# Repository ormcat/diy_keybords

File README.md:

ErgoFine
====

## 特徴
- 左右分割
- 60%
- カラムスタッカード
- ロープロファイル (Kailh Choc V1 専用)
- 狭ピッチ (18x17 MBK キャップのサイズ)

## 設計のポイント

数字行を設け、キー数に余裕をもたせたロープロファイルな 60% キーボードです。

FR4 とアクリルを積層し、硬い打鍵感を目指しました。
スイッチプレートと基盤の間にはシリコンシートを挟めると音が落ち着くかもしれません。

※基盤製造後に KiCad データを若干調整したため、なにかしら不備があるかもしれません。

---

Designed by ormcat

基盤は [自作キーボード設計入門](https://booth.pm/ja/items/1044084) を読みながら設計しました。  
KiCad シンボル、フットプリントは [foostan/kbd](https://github.com/foostan/kbd) を利用しました。

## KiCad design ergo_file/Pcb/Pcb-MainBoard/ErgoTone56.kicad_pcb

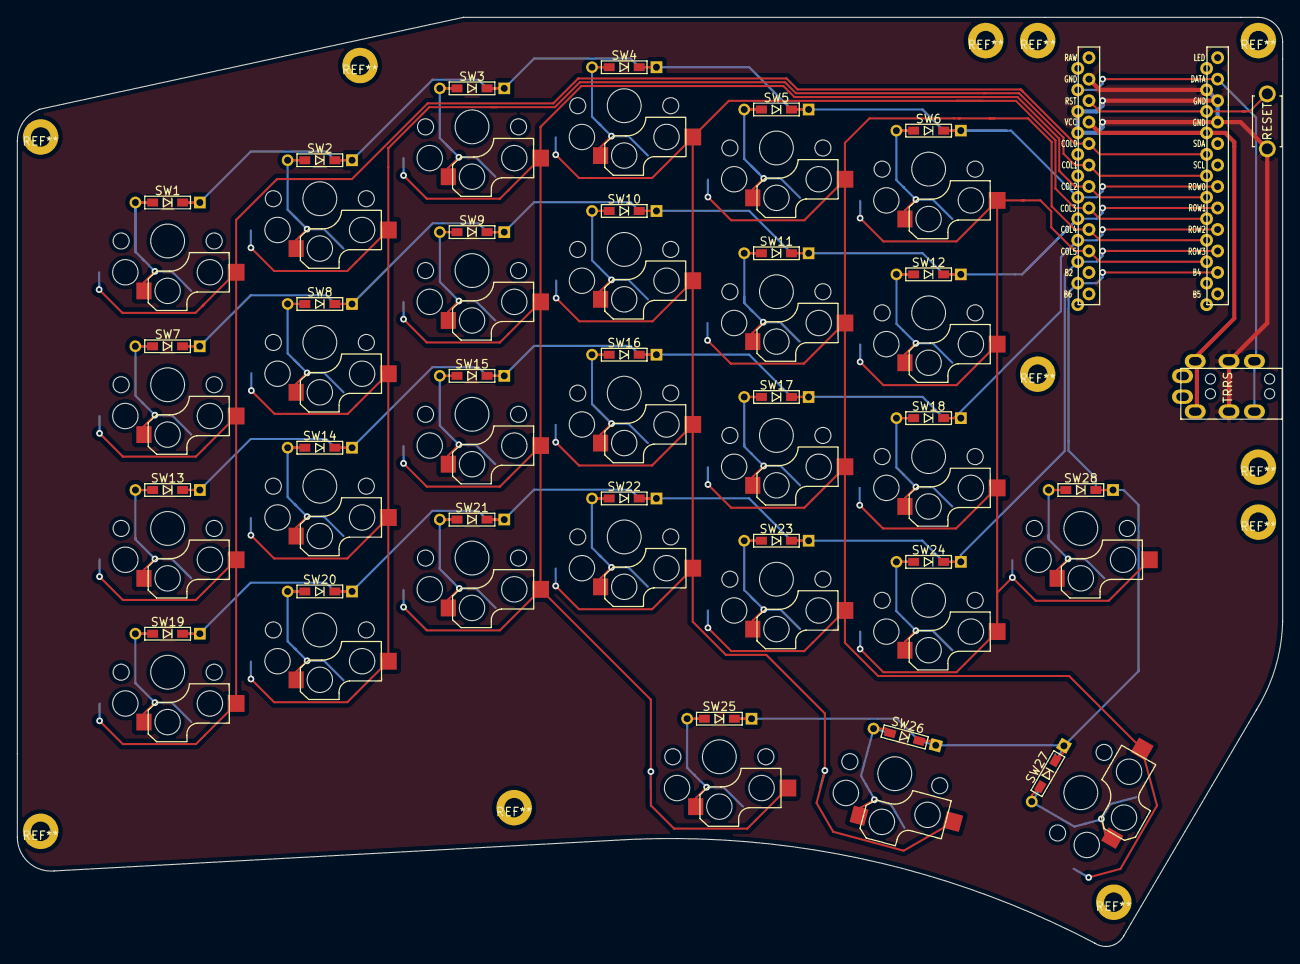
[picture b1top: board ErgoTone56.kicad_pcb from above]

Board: 2 copper layers, 149.6 x 109.9 mm, 59 parts (0 on the bottom side), 43 nets.

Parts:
D1, D2, D3, D4, D5, D6, D7, D8, D9, D10, D11, D12, D13, D14, D15, D16, D17, D18, D19, D20, D21, D22, D23, D24, D25, D26, D27, D28: D; D3_TH_SMD
J1: MJ-4PP-9
SW1, SW2, SW3, SW4, SW5, SW6, SW7, SW8, SW9, SW10, SW11, SW12, SW13, SW14, SW15, SW16, SW17, SW18, SW19, SW20, SW21, SW22, SW23, SW24, SW25, SW26, SW28: SW_PUSH; ChocV1_Hotswap_Reverse
SW27: SW_PUSH; ChocV1_Hotswap_Reverse_1.5u
SW29: SW_PUSH; ResetSW
U1: ProMicro; ProMicro_v2

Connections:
GND: J1.C, SW29.2, U1.3, U1.4, U1.23
unnamed: D1.2, SW1.2
unnamed: D2.2, SW2.2
unnamed: D3.2, SW3.2
unnamed: D4.2, SW4.2
unnamed: D5.2, SW5.2
unnamed: D6.2, SW6.2
unnamed: D7.2, SW7.2
unnamed: D8.2, SW8.2
unnamed: D9.2, SW9.2
unnamed: D10.2, SW10.2
unnamed: D11.2, SW11.2
unnamed: D12.2, SW12.2
unnamed: D13.2, SW13.2
unnamed: D14.2, SW14.2
unnamed: D15.2, SW15.2
unnamed: D16.2, SW16.2
unnamed: D17.2, SW17.2
unnamed: D18.2, SW18.2
unnamed: D19.2, SW19.2
unnamed: D20.2, SW20.2
unnamed: D21.2, SW21.2
unnamed: D22.2, SW22.2
unnamed: D23.2, SW23.2
unnamed: D24.2, SW24.2
unnamed: D25.2, SW25.2
unnamed: D26.2, SW26.2
unnamed: D27.2, SW27.2
unnamed: D28.2, SW28.2
VCC: J1.D, U1.21
col0: SW1.1, SW7.1, SW13.1, SW19.1, U1.20
col1: SW2.1, SW8.1, SW14.1, SW20.1, U1.19
col2: SW3.1, SW9.1, SW15.1, SW21.1, SW25.1, U1.18
col3: SW4.1, SW10.1, SW16.1, SW22.1, SW26.1, U1.17
col4: SW5.1, SW11.1, SW17.1, SW23.1, SW27.1, U1.16
col5: SW6.1, SW12.1, SW18.1, SW24.1, SW28.1, U1.15
data: J1.B, U1.2
reset: SW29.1, U1.22
row0: D1.1, D2.1, D3.1, D4.1, D5.1, D6.1, U1.7
row1: D7.1, D8.1, D9.1, D10.1, D11.1, D12.1, U1.8
row2: D13.1, D14.1, D15.1, D16.1, D17.1, D18.1, U1.9
row3: D19.1, D20.1, D21.1, D22.1, D23.1, D24.1, U1.10
row4: D25.1, D26.1, D27.1, D28.1, U1.11

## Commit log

2023-04-15 New Keyboard
2023-12-30 chore rm dir
2023-12-30 add hedgehog mx
2023-12-30 hifumi firmware vial
2024-05-22 Hedgehog MX add Switch Plate SVG/DXF
2024-05-31 keycap sample stl
